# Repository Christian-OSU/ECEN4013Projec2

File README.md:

# ECEN4013Projec2
Project 2 for ECEN 4013

Upload Date_Time to Teensy 4.1

Run GUI.py for serial reading
For Bluetooth, use preferred method (I used my phone, you can setup a terminal to read it) (if you have android, I can upload .apk you can install)
For CSV, it will create log file and remove previous ones if they exist

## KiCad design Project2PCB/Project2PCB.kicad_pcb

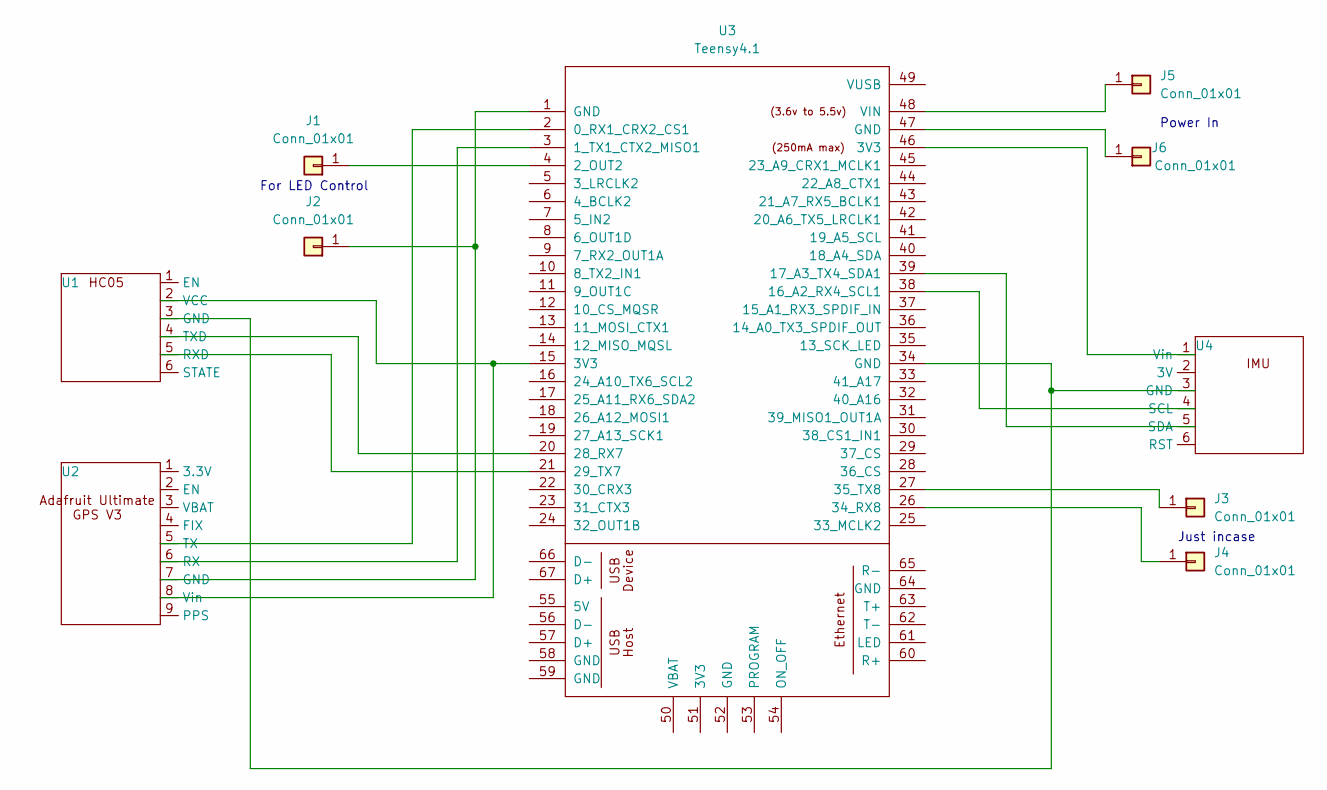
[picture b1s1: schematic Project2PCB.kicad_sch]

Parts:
J1, J2, J3, J4, J5, J6: Conn_01x01; PinSocket_1x01_P2.54mm_Vertical
U1: PinSocket_1x06_P2.54mm_Horizontal
U2: PinSocket_1x09_P2.54mm_Vertical
U3: Teensy4.1; Teensy41
U4: PinSocket_1x06_P2.54mm_Vertical

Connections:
unnamed: J1.1, U3.4 (2_OUT2)
unnamed: J2.1, U2.7 (GND), U3.1 (GND)
unnamed: J3.1, U3.27 (35_TX8)
unnamed: J4.1, U3.26 (34_RX8)
unnamed: J5.1, U3.48 (VIN)
unnamed: J6.1, U3.47 (GND)
unnamed: U1.3 (GND), U3.34 (GND), U4.3 (GND)
unnamed: U1.5 (RXD), U3.21 (29_TX7)
unnamed: U1.4 (TXD), U3.20 (28_RX7)
unnamed: U1.2 (VCC), U2.8 (Vin), U3.15 (3V3)
unnamed: U2.6 (RX), U3.3 (1_TX1_CTX2_MISO1)
unnamed: U2.5 (TX), U3.2 (0_RX1_CRX2_CS1)
unnamed: U3.38 (16_A2_RX4_SCL1), U4.4 (SCL)
unnamed: U3.39 (17_A3_TX4_SDA1), U4.5 (SDA)
unnamed: U3.46 (3V3), U4.1 (Vin)

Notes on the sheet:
Just incase
Power In
For LED Control

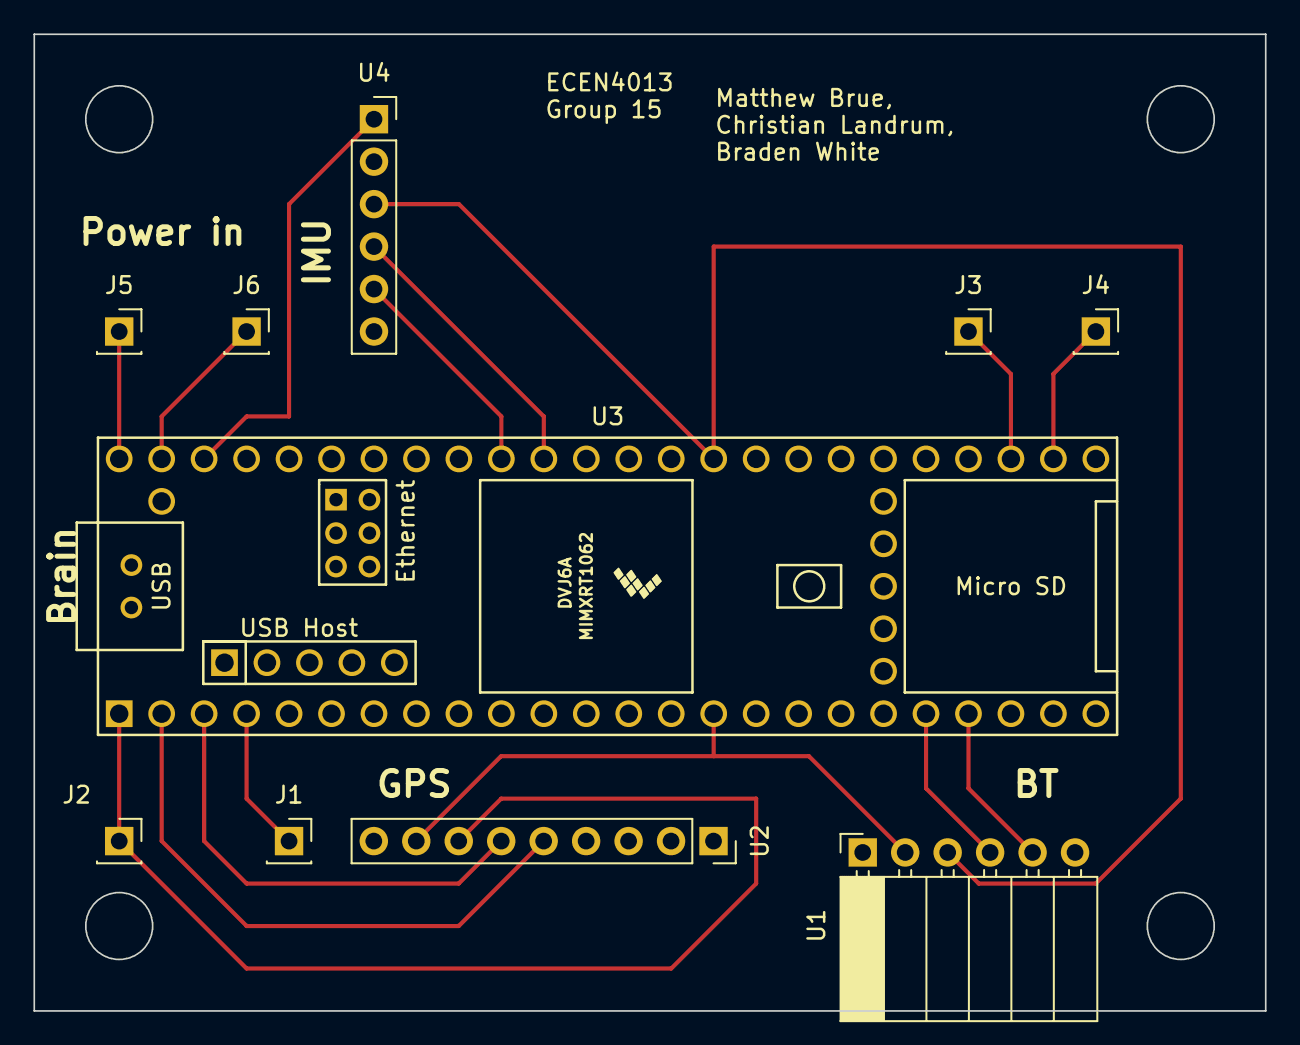
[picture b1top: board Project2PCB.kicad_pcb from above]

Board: 2 copper layers, 73.7 x 58.4 mm, 10 parts (0 on the bottom side), 15 nets.

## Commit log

2025-10-22 rough
2025-10-24 Organization
2025-10-28 ADDED GUI TESTING FOR IMU
2025-10-28 WIP Tweaking
    Begin integration has all data pulled from IMU. Need to create GUI to update with these values
2025-11-06 creating new folder for myself
2025-11-06 Changes to the GUI displaying the IMU
    altered the orientation of the box and arrows to reflect the physical IMU, Added graphs that scale based off peak values.
2025-11-06 Parses the output from the GPS
    When Serial monitoring output appears in human readable form.
2025-11-06 redundant file
2025-11-11 Matthew code for IMU and GPS
2025-11-19 Added Most recent revision
    On Teensy, load Arduino/CompletedProject
    For GUI, run SeniorProj/GUI/UseGui.py
2025-12-01 Add files via upload
    Uploaded Final Working Project Versions
2025-12-01 Update README with project setup instructions
    Added instructions for uploading to Teensy 4.1 and running GUI.py, as well as Bluetooth and CSV logging details.
2025-12-01 Add files via upload
    1 Hour test run
2025-12-02 Add files via upload
    APK of a GUI for mobile
2025-12-12 Added Videos and 1 hr CSV in zip file
2025-12-12 Add PCB files
    KiCad files are in the folder called "Project2PCB"
